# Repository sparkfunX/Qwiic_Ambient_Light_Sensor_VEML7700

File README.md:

SparkX Ambient Light Sensor - VEML7700 (Qwiic)
========================================

[*SparkX Ambient Light Sensor - VEML7700 (Qwiic) (SPX-18981)*](https://www.sparkfun.com/products/18981)

The VEML7700 is a high accuracy, 16-bit resolution, digital ambient light sensor in a miniature transparent 6.8 mm x 3.0 mm x 2.5 mm package.
It includes a high sensitivity photodiode, a low noise amplifier, a 16-bit A/D converter and supports an easy to use I<sup>2</sup>C bus communication interface.

* Filtron<sup>TM</sup> technology adaption: close to real human eye response
* O-Trim<sup>TM</sup> technology adoption: ALS output tolerance ≤ 10 %
* 16-bit dynamic range for ambient light detection from 0 lx to about 167 klx with resolution down to 0.005 lx/count
* 100 Hz and 120 Hz flicker noise rejection
* Excellent temperature compensation
* High dynamic detection resolution
* Software shutdown mode control
* High and low threshold windows with interrupt flags

Our [Arduino Library](https://github.com/sparkfun/SparkFun_VEML7700_Arduino_Library) converts the raw sensor data into lux,
automatically compensating for the sensor's gain and integration time settings.

Repository Contents
-------------------

- [**/Documents**](./Documents) - datasheets etc.
- [**/Hardware**](./Hardware) - Eagle PCB, SCH and LBR design files
- [**LICENSE.md**](./LICENSE.md) - contains the licence information

Documentation
--------------

* **[SparkFun VEML7700 Arduino Library](https://github.com/sparkfun/SparkFun_VEML7700_Arduino_Library)** - Arduino library for the ambient light sensor - VEML7700.

Product Versions
----------------

* [SPX-18981](https://www.sparkfun.com/products/18981) - Original SparkX Release.

License Information
-------------------

This product is _**open source**_!

Please review the LICENSE.md file for license information.

If you have any questions or concerns on licensing, please contact technical support on our [SparkFun forums](https://forum.sparkfun.com/viewforum.php?f=152).

Distributed as-is; no warranty is given.

- Your friends at SparkFun.

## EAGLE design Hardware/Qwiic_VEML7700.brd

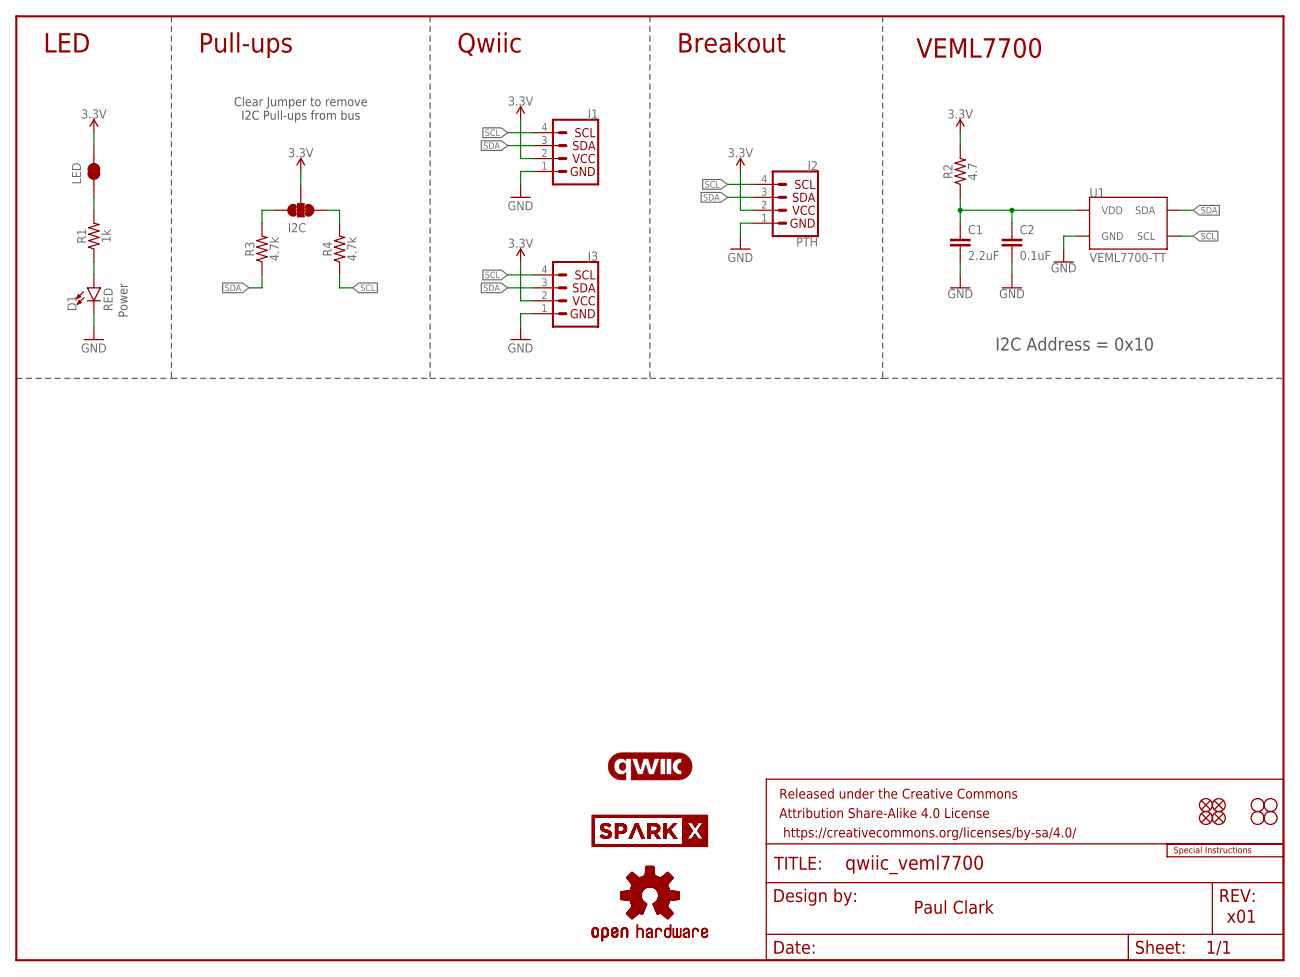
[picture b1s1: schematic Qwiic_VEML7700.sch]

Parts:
C1: 2.2uF; 0402-TIGHT
C2: 0.1uF; 0402-TIGHT
D1: RED; LED-0603
FRAME1: FRAME-LETTER; CREATIVE_COMMONS
I2C: JUMPER-SMT_3_2-NC_TRACE_SILK; SMT-JUMPER_3_2-NC_TRACE_SILK
J1, J3: Qwiic Right Angle; JST04_1MM_RA
J2: PTH; 1X04_NO_SILK
JP1, JP2, JP5, JP6: FIDUCIAL1X2; FIDUCIAL-1X2
JP3, JP4, JP7, JP8: STAND-OFF
LED: JUMPER-SMT_2_NC_TRACE_SILK; SMT-JUMPER_2_NC_TRACE_SILK
LOGO1, LOGO4: OSHW-LOGOMINI; OSHW-LOGO-MINI
LOGO2: SPECIAL_INSTRUCTIONS-ORDERING; ORDERING_INSTRUCTIONS
LOGO3: QWIIC_LOGO_5MM; QWIIC_5MM
R1: 1k; 0402-TIGHT
R2: 4.7; 0402-TIGHT
R3, R4: 4.7k; 0402-TIGHT
U1: VEML7700-TT; VEML7700_TT
U$2, U$21: SPARKX-LOGO4; SPARKX-MEDIUM

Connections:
3.3V: I2C.2, J1.2, J2.2, J3.2, LED.2, R2.2
GND: C1.2, C2.2, D1.C, J1.1, J2.1, J3.1, U1.3 (GND)
unnamed: I2C.1, R4.2
unnamed: I2C.3, R3.2
unnamed: D1.A, R1.1
unnamed: LED.1, R1.2
unnamed: C1.1, C2.1, R2.1, U1.2 (VDD)
SCL: J1.4, J2.4, J3.4, R4.1, U1.1 (SCL)
SDA: J1.3, J2.3, J3.3, R3.1, U1.4 (SDA)

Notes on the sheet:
Paul Clark
x01
Clear Jumper to remove I2C Pull-ups from bus
Power
LED
Pull-ups
Qwiic
Breakout
VEML7700
I2C Address = 0x10

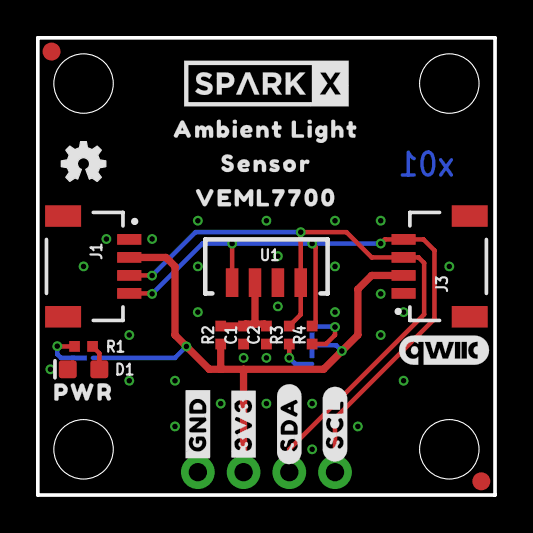
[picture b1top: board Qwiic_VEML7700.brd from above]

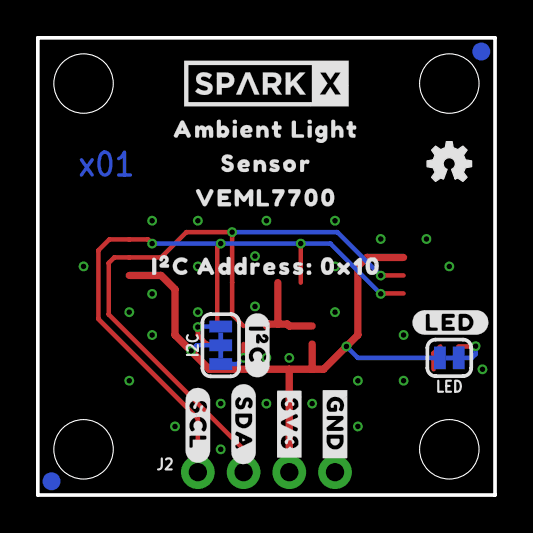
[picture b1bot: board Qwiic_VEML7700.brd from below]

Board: 2 copper layers, 25.4 x 25.4 mm, 46 parts (17 on the bottom side), 9 nets.

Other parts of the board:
U$1, U$3: #3V3#0
U$4, U$5: #GND#0
U$6, U$7: #SDA#0
U$8, U$9: #SCL#0
U$10: PWR0
U$11, U$12: AMBIENT_LIGHT0
U$13, U$14: SENSOR0
U$15, U$16: VEML77000
U$17: #I�C#0
U$18: I�C_ADDRESS#_0X100
U$19: #LED#0

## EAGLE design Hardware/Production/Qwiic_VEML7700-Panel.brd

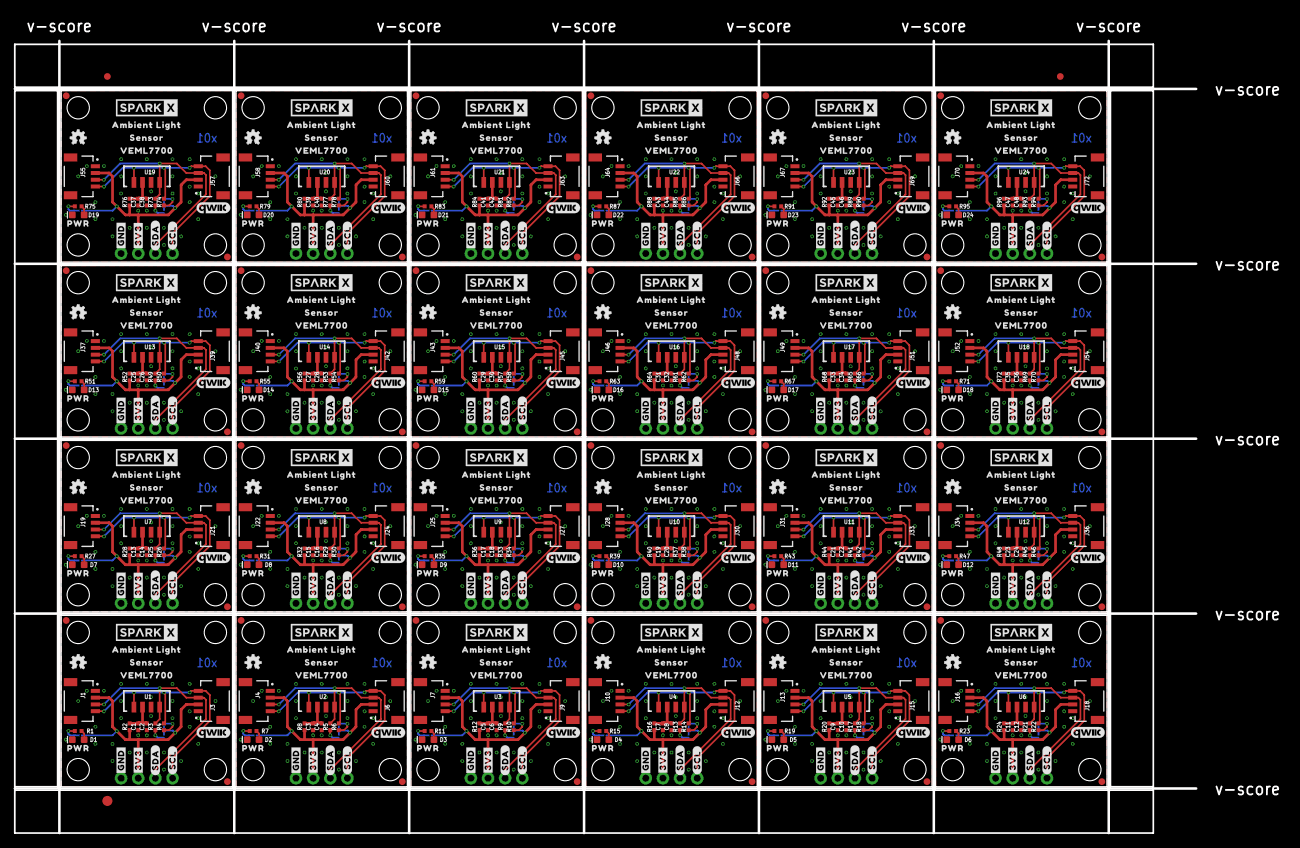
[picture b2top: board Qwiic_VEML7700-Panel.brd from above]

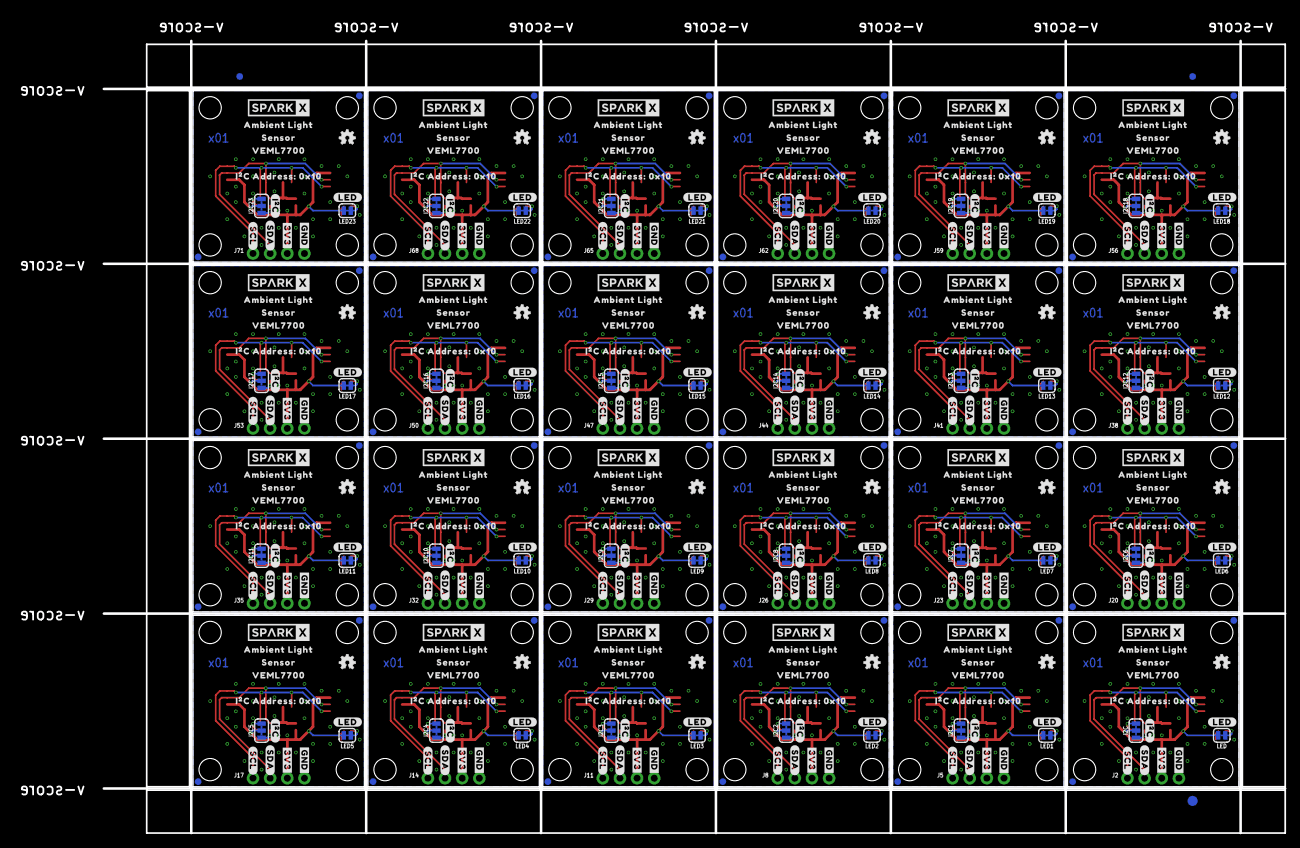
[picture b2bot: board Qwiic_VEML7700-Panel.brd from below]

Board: 2 copper layers, 188.2 x 121.2 mm, 1062 parts (411 on the bottom side), 216 nets.

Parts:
C1, C3, C5, C7, C9, C11, C13, C15, C17, C19, C21, C23, C25, C27, C29, C31, C33, C35, C37, C39, C41, C43, C45, C47: 2.2uF; 0402-TIGHT
C2, C4, C6, C8, C10, C12, C14, C16, C18, C20, C22, C24, C26, C28, C30, C32, C34, C36, C38, C40, C42, C44, C46, C48: 0.1uF; 0402-TIGHT
D1, D2, D3, D4, D5, D6, D7, D8, D9, D10, D11, D12, D13, D14, D15, D16, D17, D18, D19, D20, D21, D22, D23, D24: RED; LED-0603
E$1, E$2, E$3, E$4: FIDUCIAL-1X2
E$5, E$6: FIDUCIAL-1.5X3
I2C, I2C1, I2C2, I2C3, I2C4, I2C5, I2C6, I2C7, I2C8, I2C9, I2C10, I2C11, I2C12, I2C13, I2C14, I2C15, I2C16, I2C17, I2C18, I2C19, I2C20, I2C21, I2C22, I2C23: JUMPER-SMT_3_2-NC_TRACE_SILK; SMT-JUMPER_3_2-NC_TRACE_SILK
J1, J3, J4, J6, J7, J9, J10, J12, J13, J15, J16, J18, J19, J21, J22, J24, J25, J27, J28, J30, J31, J33, J34, J36, J37, J39, J40, J42, J43, J45, J46, J48, J49, J51, J52, J54, J55, J57, J58, J60, J61, J63, J64, J66, J67, J69, J70, J72: Qwiic Right Angle; JST04_1MM_RA
J2, J5, J8, J11, J14, J17, J20, J23, J26, J29, J32, J35, J38, J41, J44, J47, J50, J53, J56, J59, J62, J65, J68, J71: PTH; 1X04_NO_SILK
JP1, JP2, JP5, JP6, JP11, JP12, JP13, JP14, JP19, JP20, JP21, JP22, JP27, JP28, JP29, JP30, JP35, JP36, JP37, JP38, JP43, JP44, JP45, JP46, JP51, JP52, JP53, JP54, JP59, JP60, JP61, JP62, JP67, JP68, JP69, JP70, JP75, JP76, JP77, JP78, JP83, JP84, JP85, JP86, JP91, JP92, JP93, JP94, JP99, JP100, JP101, JP102, JP107, JP108, JP109, JP110, JP115, JP116, JP117, JP118, JP123, JP124, JP125, JP126, JP131, JP132, JP133, JP134, JP139, JP140, JP141, JP142, JP147, JP148, JP149, JP150, JP155, JP156, JP157, JP158, JP163, JP164, JP165, JP166, JP171, JP172, JP173, JP174, JP179, JP180, JP181, JP182, JP187, JP188, JP189, JP190: FIDUCIAL1X2; FIDUCIAL-1X2
JP3, JP4, JP7, JP8, JP9, JP10, JP15, JP16, JP17, JP18, JP23, JP24, JP25, JP26, JP31, JP32, JP33, JP34, JP39, JP40, JP41, JP42, JP47, JP48, JP49, JP50, JP55, JP56, JP57, JP58, JP63, JP64, JP65, JP66, JP71, JP72, JP73, JP74, JP79, JP80, JP81, JP82, JP87, JP88, JP89, JP90, JP95, JP96, JP97, JP98, JP103, JP104, JP105, JP106, JP111, JP112, JP113, JP114, JP119, JP120, JP121, JP122, JP127, JP128, JP129, JP130, JP135, JP136, JP137, JP138, JP143, JP144, JP145, JP146, JP151, JP152, JP153, JP154, JP159, JP160, JP161, JP162, JP167, JP168, JP169, JP170, JP175, JP176, JP177, JP178, JP183, JP184, JP185, JP186, JP191, JP192: STAND-OFF
LED, LED1, LED2, LED3, LED4, LED5, LED6, LED7, LED8, LED9, LED10, LED11, LED12, LED13, LED14, LED15, LED16, LED17, LED18, LED19, LED20, LED21, LED22, LED23: SMT-JUMPER_2_NC_TRACE_SILK
LOGO1, LOGO2, LOGO4, LOGO6, LOGO7, LOGO9, LOGO10, LOGO12, LOGO13, LOGO15, LOGO16, LOGO18, LOGO19, LOGO21, LOGO22, LOGO24, LOGO25, LOGO27, LOGO28, LOGO30, LOGO31, LOGO33, LOGO34, LOGO36, LOGO37, LOGO39, LOGO40, LOGO42, LOGO43, LOGO45, LOGO46, LOGO48, LOGO49, LOGO51, LOGO52, LOGO54, LOGO55, LOGO57, LOGO58, LOGO60, LOGO61, LOGO63, LOGO64, LOGO66, LOGO67, LOGO69, LOGO70, LOGO72: OSHW-LOGOMINI; OSHW-LOGO-MINI
LOGO3, LOGO5, LOGO8, LOGO11, LOGO14, LOGO17, LOGO20, LOGO23, LOGO26, LOGO29, LOGO32, LOGO35, LOGO38, LOGO41, LOGO44, LOGO47, LOGO50, LOGO53, LOGO56, LOGO59, LOGO62, LOGO65, LOGO68, LOGO71: QWIIC_LOGO_5MM; QWIIC_5MM
R1, R7, R11, R15, R19, R23, R27, R31, R35, R39, R43, R47, R51, R55, R59, R63, R67, R71, R75, R79, R83, R87, R91, R95: 1k; 0402-TIGHT
R2, R8, R12, R16, R20, R24, R28, R32, R36, R40, R44, R48, R52, R56, R60, R64, R68, R72, R76, R80, R84, R88, R92, R96: 4.7; 0402-TIGHT
R3, R4, R5, R6, R9, R10, R13, R14, R17, R18, R21, R22, R25, R26, R29, R30, R33, R34, R37, R38, R41, R42, R45, R46, R49, R50, R53, R54, R57, R58, R61, R62, R65, R66, R69, R70, R73, R74, R77, R78, R81, R82, R85, R86, R89, R90, R93, R94: 4.7k; 0402-TIGHT
U1, U2, U3, U4, U5, U6, U7, U8, U9, U10, U11, U12, U13, U14, U15, U16, U17, U18, U19, U20, U21, U22, U23, U24: VEML7700-TT; VEML7700_TT
U$1, U$3, U$23, U$24, U$43, U$44, U$63, U$64, U$83, U$84, U$103, U$104, U$123, U$124, U$143, U$144, U$163, U$164, U$183, U$184, U$203, U$204, U$223, U$224, U$243, U$244, U$263, U$264, U$283, U$284, U$303, U$304, U$323, U$324, U$343, U$344, U$363, U$364, U$383, U$384, U$403, U$404, U$423, U$424, U$443, U$444, U$463, U$464: #3V3#0
U$2, U$20, U$21, U$22, U$41, U$42, U$61, U$62, U$81, U$82, U$101, U$102, U$121, U$122, U$141, U$142, U$161, U$162, U$181, U$182, U$201, U$202, U$221, U$222, U$241, U$242, U$261, U$262, U$281, U$282, U$301, U$302, U$321, U$322, U$341, U$342, U$361, U$362, U$381, U$382, U$401, U$402, U$421, U$422, U$441, U$442, U$461, U$462: SPARKX-LOGO4; SPARKX-MEDIUM
U$4, U$5, U$25, U$26, U$45, U$46, U$65, U$66, U$85, U$86, U$105, U$106, U$125, U$126, U$145, U$146, U$165, U$166, U$185, U$186, U$205, U$206, U$225, U$226, U$245, U$246, U$265, U$266, U$285, U$286, U$305, U$306, U$325, U$326, U$345, U$346, U$365, U$366, U$385, U$386, U$405, U$406, U$425, U$426, U$445, U$446, U$465, U$466: #GND#0
U$6, U$7, U$27, U$28, U$47, U$48, U$67, U$68, U$87, U$88, U$107, U$108, U$127, U$128, U$147, U$148, U$167, U$168, U$187, U$188, U$207, U$208, U$227, U$228, U$247, U$248, U$267, U$268, U$287, U$288, U$307, U$308, U$327, U$328, U$347, U$348, U$367, U$368, U$387, U$388, U$407, U$408, U$427, U$428, U$447, U$448, U$467, U$468: #SDA#0
U$8, U$9, U$29, U$30, U$49, U$50, U$69, U$70, U$89, U$90, U$109, U$110, U$129, U$130, U$149, U$150, U$169, U$170, U$189, U$190, U$209, U$210, U$229, U$230, U$249, U$250, U$269, U$270, U$289, U$290, U$309, U$310, U$329, U$330, U$349, U$350, U$369, U$370, U$389, U$390, U$409, U$410, U$429, U$430, U$449, U$450, U$469, U$470: #SCL#0
U$10, U$31, U$51, U$71, U$91, U$111, U$131, U$151, U$171, U$191, U$211, U$231, U$251, U$271, U$291, U$311, U$331, U$351, U$371, U$391, U$411, U$431, U$451, U$471: PWR0
U$11, U$12, U$32, U$33, U$52, U$53, U$72, U$73, U$92, U$93, U$112, U$113, U$132, U$133, U$152, U$153, U$172, U$173, U$192, U$193, U$212, U$213, U$232, U$233, U$252, U$253, U$272, U$273, U$292, U$293, U$312, U$313, U$332, U$333, U$352, U$353, U$372, U$373, U$392, U$393, U$412, U$413, U$432, U$433, U$452, U$453, U$472, U$473: AMBIENT_LIGHT0
U$13, U$14, U$34, U$35, U$54, U$55, U$74, U$75, U$94, U$95, U$114, U$115, U$134, U$135, U$154, U$155, U$174, U$175, U$194, U$195, U$214, U$215, U$234, U$235, U$254, U$255, U$274, U$275, U$294, U$295, U$314, U$315, U$334, U$335, U$354, U$355, U$374, U$375, U$394, U$395, U$414, U$415, U$434, U$435, U$454, U$455, U$474, U$475: SENSOR0
U$15, U$16, U$36, U$37, U$56, U$57, U$76, U$77, U$96, U$97, U$116, U$117, U$136, U$137, U$156, U$157, U$176, U$177, U$196, U$197, U$216, U$217, U$236, U$237, U$256, U$257, U$276, U$277, U$296, U$297, U$316, U$317, U$336, U$337, U$356, U$357, U$376, U$377, U$396, U$397, U$416, U$417, U$436, U$437, U$456, U$457, U$476, U$477: VEML77000
U$17, U$38, U$58, U$78, U$98, U$118, U$138, U$158, U$178, U$198, U$218, U$238, U$258, U$278, U$298, U$318, U$338, U$358, U$378, U$398, U$418, U$438, U$458, U$478: #I�C#0
U$18, U$39, U$59, U$79, U$99, U$119, U$139, U$159, U$179, U$199, U$219, U$239, U$259, U$279, U$299, U$319, U$339, U$359, U$379, U$399, U$419, U$439, U$459, U$479: I�C_ADDRESS#_0X100
U$19, U$40, U$60, U$80, U$100, U$120, U$140, U$160, U$180, U$200, U$220, U$240, U$260, U$280, U$300, U$320, U$340, U$360, U$380, U$400, U$420, U$440, U$460, U$480: #LED#0

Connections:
3.3V: I2C.2, J1.2, J2.2, J3.2, LED.2, R2.2
3.3V1: I2C1.2, J4.2, J5.2, J6.2, LED1.2, R8.2
3.3V2: I2C2.2, J7.2, J8.2, J9.2, LED2.2, R12.2
3.3V3: I2C3.2, J10.2, J11.2, J12.2, LED3.2, R16.2
3.3V4: I2C4.2, J13.2, J14.2, J15.2, LED4.2, R20.2
3.3V5: I2C5.2, J16.2, J17.2, J18.2, LED5.2, R24.2
3.3V6: I2C6.2, J19.2, J20.2, J21.2, LED6.2, R28.2
3.3V7: I2C7.2, J22.2, J23.2, J24.2, LED7.2, R32.2
3.3V8: I2C8.2, J25.2, J26.2, J27.2, LED8.2, R36.2
3.3V9: I2C9.2, J28.2, J29.2, J30.2, LED9.2, R40.2
3.3V10: I2C10.2, J31.2, J32.2, J33.2, LED10.2, R44.2
3.3V11: I2C11.2, J34.2, J35.2, J36.2, LED11.2, R48.2
3.3V12: I2C12.2, J37.2, J38.2, J39.2, LED12.2, R52.2
3.3V13: I2C13.2, J40.2, J41.2, J42.2, LED13.2, R56.2
3.3V14: I2C14.2, J43.2, J44.2, J45.2, LED14.2, R60.2
3.3V15: I2C15.2, J46.2, J47.2, J48.2, LED15.2, R64.2
3.3V16: I2C16.2, J49.2, J50.2, J51.2, LED16.2, R68.2
3.3V17: I2C17.2, J52.2, J53.2, J54.2, LED17.2, R72.2
3.3V18: I2C18.2, J55.2, J56.2, J57.2, LED18.2, R76.2
3.3V19: I2C19.2, J58.2, J59.2, J60.2, LED19.2, R80.2
3.3V20: I2C20.2, J61.2, J62.2, J63.2, LED20.2, R84.2
3.3V21: I2C21.2, J64.2, J65.2, J66.2, LED21.2, R88.2
3.3V22: I2C22.2, J67.2, J68.2, J69.2, LED22.2, R92.2
3.3V23: I2C23.2, J70.2, J71.2, J72.2, LED23.2, R96.2
GND: C1.2, C2.2, D1.C, J1.1, J2.1, J3.1, U1.3
GND1: C3.2, C4.2, D2.C, J4.1, J5.1, J6.1, U2.3
GND2: C5.2, C6.2, D3.C, J7.1, J8.1, J9.1, U3.3
GND3: C7.2, C8.2, D4.C, J10.1, J11.1, J12.1, U4.3
GND4: C9.2, C10.2, D5.C, J13.1, J14.1, J15.1, U5.3
GND5: C11.2, C12.2, D6.C, J16.1, J17.1, J18.1, U6.3
GND6: C13.2, C14.2, D7.C, J19.1, J20.1, J21.1, U7.3
GND7: C15.2, C16.2, D8.C, J22.1, J23.1, J24.1, U8.3
GND8: C17.2, C18.2, D9.C, J25.1, J26.1, J27.1, U9.3
GND9: C19.2, C20.2, D10.C, J28.1, J29.1, J30.1, U10.3
GND10: C21.2, C22.2, D11.C, J31.1, J32.1, J33.1, U11.3
GND11: C23.2, C24.2, D12.C, J34.1, J35.1, J36.1, U12.3
GND12: C25.2, C26.2, D13.C, J37.1, J38.1, J39.1, U13.3
GND13: C27.2, C28.2, D14.C, J40.1, J41.1, J42.1, U14.3
GND14: C29.2, C30.2, D15.C, J43.1, J44.1, J45.1, U15.3
GND15: C31.2, C32.2, D16.C, J46.1, J47.1, J48.1, U16.3
GND16: C33.2, C34.2, D17.C, J49.1, J50.1, J51.1, U17.3
GND17: C35.2, C36.2, D18.C, J52.1, J53.1, J54.1, U18.3
GND18: C37.2, C38.2, D19.C, J55.1, J56.1, J57.1, U19.3
GND19: C39.2, C40.2, D20.C, J58.1, J59.1, J60.1, U20.3
GND20: C41.2, C42.2, D21.C, J61.1, J62.1, J63.1, U21.3
GND21: C43.2, C44.2, D22.C, J64.1, J65.1, J66.1, U22.3
GND22: C45.2, C46.2, D23.C, J67.1, J68.1, J69.1, U23.3
GND23: C47.2, C48.2, D24.C, J70.1, J71.1, J72.1, U24.3
unnamed: I2C.1, R4.2
unnamed: I2C.3, R3.2
unnamed: D1.A, R1.1
unnamed: LED.1, R1.2
unnamed: C1.1, C2.1, R2.1, U1.2
unnamed: I2C1.1, R6.2
unnamed: I2C1.3, R5.2
unnamed: D2.A, R7.1
unnamed: LED1.1, R7.2
unnamed: C3.1, C4.1, R8.1, U2.2
unnamed: I2C2.1, R10.2
unnamed: I2C2.3, R9.2
unnamed: D3.A, R11.1
unnamed: LED2.1, R11.2
unnamed: C5.1, C6.1, R12.1, U3.2
unnamed: I2C3.1, R14.2
unnamed: I2C3.3, R13.2
unnamed: D4.A, R15.1
unnamed: LED3.1, R15.2
unnamed: C7.1, C8.1, R16.1, U4.2
unnamed: I2C4.1, R18.2
unnamed: I2C4.3, R17.2
unnamed: D5.A, R19.1
unnamed: LED4.1, R19.2
unnamed: C9.1, C10.1, R20.1, U5.2
unnamed: I2C5.1, R22.2
unnamed: I2C5.3, R21.2
unnamed: D6.A, R23.1
unnamed: LED5.1, R23.2
unnamed: C11.1, C12.1, R24.1, U6.2
unnamed: I2C6.1, R26.2
unnamed: I2C6.3, R25.2
unnamed: D7.A, R27.1
unnamed: LED6.1, R27.2
unnamed: C13.1, C14.1, R28.1, U7.2
unnamed: I2C7.1, R30.2
unnamed: I2C7.3, R29.2
unnamed: D8.A, R31.1
unnamed: LED7.1, R31.2
unnamed: C15.1, C16.1, R32.1, U8.2
unnamed: I2C8.1, R34.2
unnamed: I2C8.3, R33.2
unnamed: D9.A, R35.1
unnamed: LED8.1, R35.2
unnamed: C17.1, C18.1, R36.1, U9.2
unnamed: I2C9.1, R38.2
unnamed: I2C9.3, R37.2
unnamed: D10.A, R39.1
unnamed: LED9.1, R39.2
unnamed: C19.1, C20.1, R40.1, U10.2
unnamed: I2C10.1, R42.2
unnamed: I2C10.3, R41.2
unnamed: D11.A, R43.1
unnamed: LED10.1, R43.2
unnamed: C21.1, C22.1, R44.1, U11.2
unnamed: I2C11.1, R46.2
unnamed: I2C11.3, R45.2
unnamed: D12.A, R47.1
unnamed: LED11.1, R47.2
unnamed: C23.1, C24.1, R48.1, U12.2
unnamed: I2C12.1, R50.2
unnamed: I2C12.3, R49.2
unnamed: D13.A, R51.1
unnamed: LED12.1, R51.2
unnamed: C25.1, C26.1, R52.1, U13.2
unnamed: I2C13.1, R54.2
unnamed: I2C13.3, R53.2
unnamed: D14.A, R55.1
unnamed: LED13.1, R55.2
unnamed: C27.1, C28.1, R56.1, U14.2
unnamed: I2C14.1, R58.2
unnamed: I2C14.3, R57.2
unnamed: D15.A, R59.1
unnamed: LED14.1, R59.2
unnamed: C29.1, C30.1, R60.1, U15.2
unnamed: I2C15.1, R62.2
unnamed: I2C15.3, R61.2
unnamed: D16.A, R63.1
unnamed: LED15.1, R63.2
unnamed: C31.1, C32.1, R64.1, U16.2
unnamed: I2C16.1, R66.2
unnamed: I2C16.3, R65.2
unnamed: D17.A, R67.1
unnamed: LED16.1, R67.2
unnamed: C33.1, C34.1, R68.1, U17.2
unnamed: I2C17.1, R70.2
unnamed: I2C17.3, R69.2
unnamed: D18.A, R71.1
unnamed: LED17.1, R71.2
unnamed: C35.1, C36.1, R72.1, U18.2
unnamed: I2C18.1, R74.2
unnamed: I2C18.3, R73.2
unnamed: D19.A, R75.1
unnamed: LED18.1, R75.2
unnamed: C37.1, C38.1, R76.1, U19.2
unnamed: I2C19.1, R78.2
unnamed: I2C19.3, R77.2
unnamed: D20.A, R79.1
unnamed: LED19.1, R79.2
unnamed: C39.1, C40.1, R80.1, U20.2
unnamed: I2C20.1, R82.2
unnamed: I2C20.3, R81.2
unnamed: D21.A, R83.1
unnamed: LED20.1, R83.2
unnamed: C41.1, C42.1, R84.1, U21.2
unnamed: I2C21.1, R86.2
unnamed: I2C21.3, R85.2
unnamed: D22.A, R87.1
unnamed: LED21.1, R87.2
unnamed: C43.1, C44.1, R88.1, U22.2
unnamed: I2C22.1, R90.2
unnamed: I2C22.3, R89.2
unnamed: D23.A, R91.1
unnamed: LED22.1, R91.2
unnamed: C45.1, C46.1, R92.1, U23.2
unnamed: I2C23.1, R94.2
unnamed: I2C23.3, R93.2
unnamed: D24.A, R95.1
unnamed: LED23.1, R95.2
unnamed: C47.1, C48.1, R96.1, U24.2
SCL: J1.4, J2.4, J3.4, R4.1, U1.1
SCL1: J4.4, J5.4, J6.4, R6.1, U2.1
SCL2: J7.4, J8.4, J9.4, R10.1, U3.1
SCL3: J10.4, J11.4, J12.4, R14.1, U4.1
SCL4: J13.4, J14.4, J15.4, R18.1, U5.1
SCL5: J16.4, J17.4, J18.4, R22.1, U6.1
SCL6: J19.4, J20.4, J21.4, R26.1, U7.1
SCL7: J22.4, J23.4, J24.4, R30.1, U8.1
SCL8: J25.4, J26.4, J27.4, R34.1, U9.1
SCL9: J28.4, J29.4, J30.4, R38.1, U10.1
SCL10: J31.4, J32.4, J33.4, R42.1, U11.1
SCL11: J34.4, J35.4, J36.4, R46.1, U12.1
SCL12: J37.4, J38.4, J39.4, R50.1, U13.1
SCL13: J40.4, J41.4, J42.4, R54.1, U14.1
SCL14: J43.4, J44.4, J45.4, R58.1, U15.1
SCL15: J46.4, J47.4, J48.4, R62.1, U16.1
SCL16: J49.4, J50.4, J51.4, R66.1, U17.1
SCL17: J52.4, J53.4, J54.4, R70.1, U18.1
SCL18: J55.4, J56.4, J57.4, R74.1, U19.1
SCL19: J58.4, J59.4, J60.4, R78.1, U20.1
SCL20: J61.4, J62.4, J63.4, R82.1, U21.1
SCL21: J64.4, J65.4, J66.4, R86.1, U22.1
SCL22: J67.4, J68.4, J69.4, R90.1, U23.1
SCL23: J70.4, J71.4, J72.4, R94.1, U24.1
SDA: J1.3, J2.3, J3.3, R3.1, U1.4
SDA1: J4.3, J5.3, J6.3, R5.1, U2.4
SDA2: J7.3, J8.3, J9.3, R9.1, U3.4
SDA3: J10.3, J11.3, J12.3, R13.1, U4.4
SDA4: J13.3, J14.3, J15.3, R17.1, U5.4
SDA5: J16.3, J17.3, J18.3, R21.1, U6.4
SDA6: J19.3, J20.3, J21.3, R25.1, U7.4
SDA7: J22.3, J23.3, J24.3, R29.1, U8.4
SDA8: J25.3, J26.3, J27.3, R33.1, U9.4
SDA9: J28.3, J29.3, J30.3, R37.1, U10.4
SDA10: J31.3, J32.3, J33.3, R41.1, U11.4
SDA11: J34.3, J35.3, J36.3, R45.1, U12.4
SDA12: J37.3, J38.3, J39.3, R49.1, U13.4
SDA13: J40.3, J41.3, J42.3, R53.1, U14.4
SDA14: J43.3, J44.3, J45.3, R57.1, U15.4
SDA15: J46.3, J47.3, J48.3, R61.1, U16.4
SDA16: J49.3, J50.3, J51.3, R65.1, U17.4
SDA17: J52.3, J53.3, J54.3, R69.1, U18.4
SDA18: J55.3, J56.3, J57.3, R73.1, U19.4
SDA19: J58.3, J59.3, J60.3, R77.1, U20.4
SDA20: J61.3, J62.3, J63.3, R81.1, U21.4
SDA21: J64.3, J65.3, J66.3, R85.1, U22.4
SDA22: J67.3, J68.3, J69.3, R89.1, U23.4
SDA23: J70.3, J71.3, J72.3, R93.1, U24.4

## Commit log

2021-11-05 Add dimensions and measures
2022-01-10 Add product image

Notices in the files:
parts and their libraries:
SparkFun-Resistors: Licensing: Creative Commons ShareAlike 4.0 International - https://creativecommons.org/licenses/by-sa/4.0
SparkFun-Aesthetics: Released under the Creative Commons Attribution Share-Alike 4.0 License
SparkFun-Aesthetics: https://creativecommons.org/licenses/by-sa/4.0
